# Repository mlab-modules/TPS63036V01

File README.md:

# TPS63036V01 -  TPS63036-Based  buck-boost converter 

The TPS63036V01 module is a highly efficient, single-inductor, buck-boost converter designed to provide a stable output voltage from varying input voltages. It integrates the Texas Instruments TPS63036 chip, making it suitable for applications requiring a compact, efficient power solution.

## Features

- **Input Voltage Range:** 1.8V to 5.5V
- **Output Voltage:** 3.3V (adjustable between 1.2V and 5.5V)
- **Maximum Output Current:** 600 mA
- **Operating Frequency:** 2 MHz
- **High Efficiency:** Up to 85% at 3.6V input and 500mA load
- **Compact Size:** Miniature 3.0 × 3.0 mm footprint
- **Shielded Inductors:** LPS3015 series for low DCR and excellent current handling

## Components

### TPS63036 Buck-Boost Converter
- **Manufacturer:** Texas Instruments
- **Package:** 8-ball, 1.854 mm × 1.076 mm wafer chip-scale package (YFG)
- **Description:** The TPS63036 is a highly efficient single-inductor buck-boost converter. It supports both fixed and adjustable output voltages. The device operates with an input voltage range of 1.8V to 5.5V.

### LPS3015 Series Shielded Inductors
- **Manufacturer:** Coilcraft
- **Inductance Values:** Range from 1.0 µH to 330 µH
- **DCR (max):** 0.075 to 23.0 ohms
- **Current Rating:** Up to 2.35A
- **SRF (min):** 9 MHz
- **Dimensions:** 3.0 × 3.0 mm footprint, less than 1.5 mm tall

## Setup Instructions

1. **Input Connection:** Connect the input power supply between on input header. Ensure the input voltage is between 1.8V and 5.5V.
2. **Output Connection:** Connect the load to output header.
3. **Enable/Disable:** Use jumper SV1 to enable or disable the TPS63036.
4. **Power-Saving Mode:** Use jumper SV6 to enable (PWM/PSM) or disable (PWM) the power-saving mode.

## Performance Specifications

| Parameter       | Condition                  | Min  | Typ  | Max  | Unit |
|-----------------|----------------------------|------|------|------|------|
| Input Voltage   |                            | 1.8  | 5.5  |      | V    |
| Output Voltage  | Vin = 4.2V, Iout = 500mA   | 3.2  | 3.3  | 3.4  | V    |
| Output Current  | Vin = 3.6V                 | 0    | 600  |      | mA   |
| Operating Freq. |                            |      | 2000 |      | kHz  |
| Efficiency      | 3.6V in, 500mA load        |      | 85   |      | %    |
| Output Ripple   | 3.6V in, 500mA load        |      | 25   |      | mV   |

## Additional Resources

- [TPS63036 Datasheet](https://www.ti.com/lit/ds/symlink/tps63036.pdf)
- [LPS3015 Inductor Datasheet](https://www.coilcraft.com/en-us/products/inductors/shielded/lps3015/)

## Contact

For support, contact MLAB at [support@mlab.cz](mailto:support@mlab.cz).

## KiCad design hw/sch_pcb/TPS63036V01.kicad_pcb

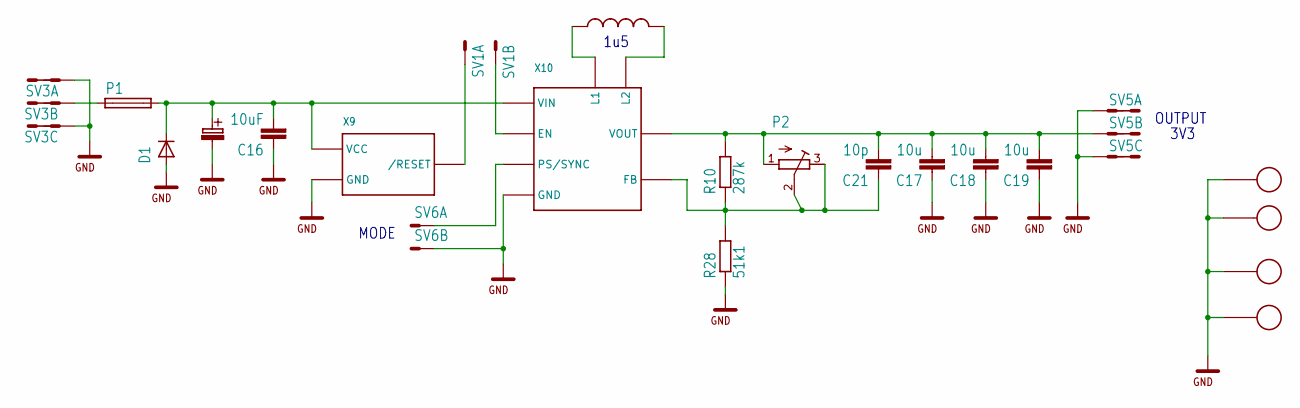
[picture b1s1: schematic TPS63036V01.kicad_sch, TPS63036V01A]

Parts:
C16: 10uF; C0805
C17, C18, C19: 10u; C0805
C20: 47uF; B
C21: 10p; 0603
D1: D-OB.SMA; SMA
L2: LPS3015-152MLC; LPS3015
P1: POJISTKA_1812; 1812
P2: TRIM_CA9MTV10
R10: 287k; 0603
R28: 51k1; 0603
SV1, SV6: MA02-1
SV3, SV5: MA03-2
X1, X2, X3, X4: SROUB3M
X9: APX809-26SA; SOT23
X10: TPS63036; DSBGA8

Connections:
+BAT2: C16.2, C20.+ (C_EL+), D1.K (C), P1.2, X9.3 (VCC), X10.A1 (VIN)
GND: C16.1, C17.1, C18.1, C19.1, C20.- (C_EL-), D1.A, R28.1, SV3.1, SV3.2, SV3.5, SV3.6, SV5.1, SV5.2, SV5.5, SV5.6, SV6.2, X1.P$1, X2.P$1, X3.P$1, X4.P$1, X9.1 (GND), X10.C2 (GND)
unnamed: SV1.1, X9.2 (/RESET)
unnamed: SV1.2, X10.A2 (EN)
unnamed: P1.1, SV3.3, SV3.4
unnamed: L2.1-1 (1), L2.1-2 (1), L2.1-3 (1), X10.B1 (L1)
unnamed: SV6.1, X10.B2 (PS/SYNC)
unnamed: L2.2-1 (2), L2.2-2 (2), L2.2-3 (2), X10.C1 (L2)
unnamed: C17.2, C18.2, C19.2, C21.2, P2.1, R10.2, SV5.3, SV5.4, X10.D1 (VOUT)
unnamed: C21.1, P2.2, P2.3, R10.1, R28.2, X10.D2 (FB)

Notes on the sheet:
MODE
3V3
1u5
OUTPUT

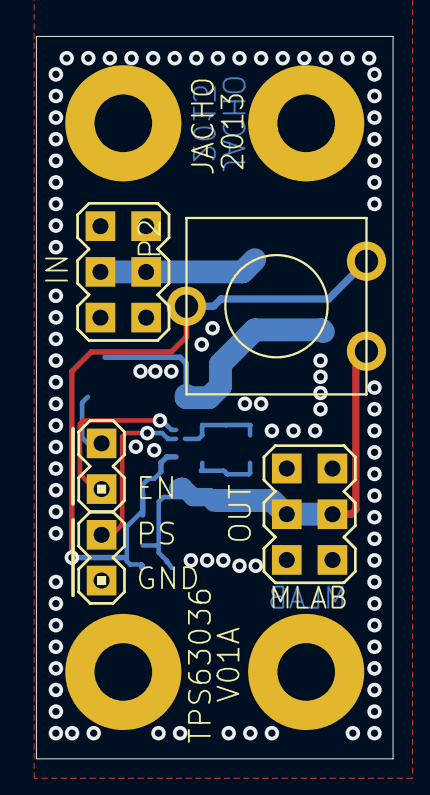
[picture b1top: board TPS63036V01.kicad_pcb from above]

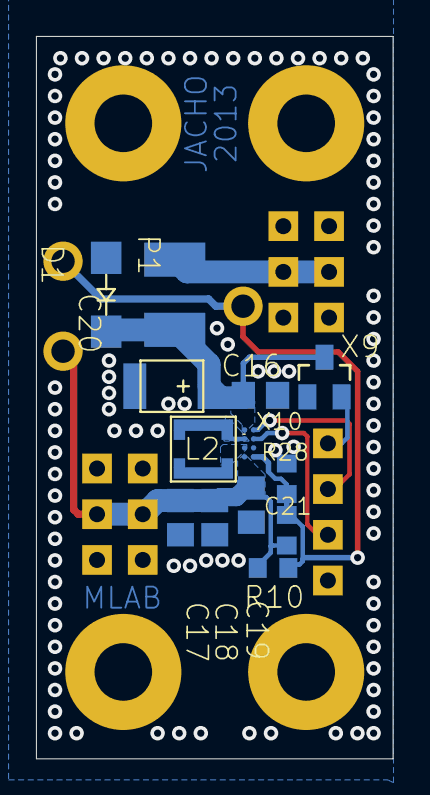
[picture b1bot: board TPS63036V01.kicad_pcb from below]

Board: 2 copper layers, 19.8 x 40.1 mm, 22 parts (13 on the bottom side), 10 nets.

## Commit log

2023-04-01 Adding force option to enable splitting in not fresh copy of Modules repository.
2023-09-17 automated commit; add github actions
2023-09-17 Update metadata files
2023-09-17 Update workflow files
2024-07-06 Convert Eagle project to KiCADv7.
2024-07-06 Update actions products
2024-07-06 Improve documentation.
